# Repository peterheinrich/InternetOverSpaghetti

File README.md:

# IP_Over_Spaghetti
Transmitting IP packages using two spaghetti as transport medium

Actually this is rather RS232 over spaghetti. But using the SLIP protocol, some USB-to-RS232 adapters and two Linux machines, one can easily tunnel IP over RS232, thus effectively tunneling IP over the spaghetti.

The whole chain looks like this:
SLIP(Linux) -> FTDI (USB<->RS232) -> ATMega328P -> Relais -> Spaghetti -> Optical Sensor -> ATMega328P -> FTDI (USB<->RS232) -> SLIP(Linux)

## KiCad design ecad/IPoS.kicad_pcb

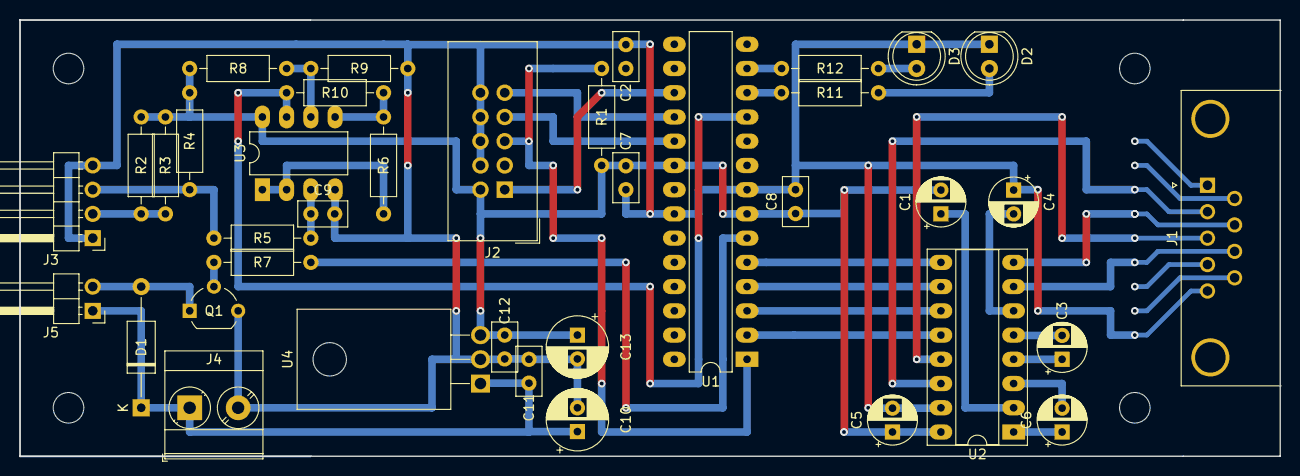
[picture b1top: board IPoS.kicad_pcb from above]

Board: 2 copper layers, 132.1 x 45.7 mm, 42 parts (0 on the bottom side), 35 nets.

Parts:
C1, C3, C4, C5, C6: 1u; CP_Radial_D5.0mm_P2.50mm
C2, C7, C8, C9, C11, C12: 100n; C_Disc_D5.0mm_W2.5mm_P2.50mm
C10, C13: 100u; CP_Radial_D6.3mm_P2.50mm
D1: D; D_A-405_P12.70mm_Horizontal
D2: LED RD; LED_D5.0mm
D3: LED GN; LED_D5.0mm
J1: RS232; DSUB-9_Female_Horizontal_P2.77x2.84mm_EdgePinOffset4.94mm_H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
J2: AVR-ISP-10; IDC-Header_2x05_P2.54mm_Vertical
J3: Optical Sensor; PinHeader_1x04_P2.54mm_Horizontal
J4: Power In; TerminalBlock_Phoenix_MKDS-3-2-5.08_1x02_P5.08mm_Horizontal
J5: Relais; PinHeader_1x02_P2.54mm_Horizontal
MH1, MH2, MH3, MH4: MountingHole; MountingHole_3.2mm_M3
Q1: BC547; TO-92_Wide
R1, R5, R10: 10K; R_Axial_DIN0207_L6.3mm_D2.5mm_P10.16mm_Horizontal
R2, R3: 150; R_Axial_DIN0207_L6.3mm_D2.5mm_P10.16mm_Horizontal
R4, R7, R8, R9: 3K3; R_Axial_DIN0207_L6.3mm_D2.5mm_P10.16mm_Horizontal
R6, R11, R12: 1K; R_Axial_DIN0207_L6.3mm_D2.5mm_P10.16mm_Horizontal
U1: ATMega328; DIP-28_W7.62mm_LongPads
U2: MAX232; DIP-16_W7.62mm_Socket_LongPads
U3: LM358; DIP-8_W7.62mm_LongPads
U4: L7805; TO-220F-3_Horizontal_TabDown

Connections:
+5V: C1.2, C5.1, C7.1, C8.1, C12.1, C13.1, J2.2, R1.1, R2.1, R3.1, R4.1, R8.1, U1.7, U1.20, U2.16, U3.8, U4.3
+12V: C10.1, C11.1, D1.1, J4.1, J5.1, U4.1
/CTS: U1.5, U2.9
/MISO: J2.9, U1.18
/MOSI: J2.1, U1.17
/RS232_CTS: J1.8, U2.7
/RS232_RTS: J1.7, U2.8
/RS232_RXD: J1.2, U2.14
/RS232_TXD: J1.3, U2.13
/RTS: U1.4, U2.10
/RXD: U1.2, U2.12
/Spaghetti_RX: R10.1, U1.11, U3.7
/Spaghetti_TX: R7.2, U1.6
/TXD: U1.3, U2.11
GND: C2.2, C4.1, C5.2, C7.2, C8.2, C9.2, C10.2, C11.2, C12.2, C13.2, D2.1, D3.1, J1.5, J2.4, J2.6, J2.8, J2.10, J3.1, J3.4, J4.2, Q1.3, R9.2, U1.8, U1.22, U2.15, U3.4, U4.2
unnamed: C1.1, U2.2
unnamed: C2.1, J2.5, R1.2, U1.1
unnamed: C3.1, U2.4
unnamed: C3.2, U2.5
unnamed: C4.2, U2.6
unnamed: C6.1, U2.1
unnamed: C6.2, U2.3
unnamed: C9.1, R5.1, U3.3
unnamed: D1.2, J5.2, Q1.1
unnamed: D2.2, R11.1
unnamed: D3.2, R12.1
unnamed: J2.7, U1.19
unnamed: J3.2, R2.2, R3.2
unnamed: J3.3, R4.2, R5.2
unnamed: Q1.2, R7.1
unnamed: R6.2, U3.1, U3.2
unnamed: R8.2, R9.1, U3.6
unnamed: R6.1, R10.2, U3.5
unnamed: R11.2, U1.12
unnamed: R12.2, U1.13

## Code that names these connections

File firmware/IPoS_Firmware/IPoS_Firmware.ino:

#include "TimerOne.h"  

#define SPAGHETTI_RX  5
#define SPAGHETTI_TX  4
#define LED_RED       6
#define LED_GREEN     7
#define CTS           3
#define RTS           2

#define BUFFSIZE      32
#define __DEBUG__

// Global variables need 'volatile' so that they can be altered within the ISR routine
volatile int tick = 0;

volatile char tx_buff[BUFFSIZE];
volatile char tx_buff_last = 0;
volatile char tx_byte = 0;
volatile char tx_state = 0;
volatile char tx_bit = 0;
volatile char tx_blank = 0;

volatile char rx_byte = 0;
volatile char rx_state = 0;
volatile char rx_bit = 0;
volatile char rx_tick_offset = 0;

/* ********************************************************************** */
/* *** BOARD SETUP                                                    *** */
/* ********************************************************************** */
void setup() {

  // Setup board specific pins
  pinMode(SPAGHETTI_TX, OUTPUT);
  pinMode(SPAGHETTI_RX, INPUT);
  pinMode(LED_RED, OUTPUT);
  pinMode(LED_GREEN, OUTPUT);
  pinMode(CTS, INPUT);
  pinMode(RTS, OUTPUT);

  // Simple 9600 8N1
  Serial.begin(9600); 

  // Assert RTS to accept incomming bytes
  digitalWrite(RTS,LOW);
  
  // Initialize 2.5ms timer interupt and register isr
  Timer1.initialize(2500);
  Timer1.attachInterrupt(isr_timer);

}


/* ********************************************************************** */
/* *** MAIN 400Hz INTERRUPT ROUTINE                                    *** */
/* ********************************************************************** */
void isr_timer() {
  int i;

  /* ********************************************************************** */
  /* *** TRANSMIT                                                       *** */
  /* ********************************************************************** */

  // Check if buffer is full. If buffer is full it is better to lose bytes than to crash ...
  if (Serial.available() > 0 && tx_buff_last < BUFFSIZE - 1) {
    tx_buff[tx_buff_last] = Serial.read() & 0xFF;
    tx_buff_last++;
  } 

  // Some implementation take several bytes until they react on RTS deassertion. Thus, we accept only 4 bytes before deasserting RTS.
  if(tx_buff_last > 3) {
      digitalWrite(RTS,HIGH);
  }
  else {
      digitalWrite(RTS,LOW);
  }

  // A single bit is exactly 25ms long. Thus, we switch states every 10 timer ticks.
  if(tick % 10 == 0) {
    switch(tx_state) {
      case 0:
       // If buffer is nonempty, remove and transmit first byte from buffer
        if(tx_buff_last > 0) {
          tx_byte = tx_buff[0];
          // move all items to the front - yes, dumb but simple! No need for a ringbuffer whatsoever!
          for(i = 1; i < tx_buff_last; i++) {
            tx_buff[i-1] = tx_buff[i];
          }
          tx_buff_last --;
          tx_state = 1;
          tx_bit = 0;
        }
        break;
      case 1:
        // Write the start bit
        digitalWrite(SPAGHETTI_TX,HIGH);
        tx_state = 2;
        break;
      case 2:
        // Write individual bits
        digitalWrite(SPAGHETTI_TX,(tx_byte >> tx_bit) & 0x01);
        tx_bit++;
        if(tx_bit > 7) {
          tx_blank = 0;
          tx_state = 3;
          tx_bit = 0;
        }
        break;
      case 3:
        // Insert a two cycle blank
        digitalWrite(SPAGHETTI_TX,LOW);
        if(tx_blank > 1) {
          tx_state = 0;
        }
        tx_blank ++;
        break;
    }   
  }

  /* ********************************************************************** */
  /* *** RECEIVE                                                        *** */
  /* ********************************************************************** */
  
  // We scan for the start bit on any tick (400Hz)
  if(rx_state == 0) {
    if(digitalRead(SPAGHETTI_RX)) {

#ifdef __DEBUG__
      digitalWrite(LED_RED,HIGH);
      delay(1);
      digitalWrite(LED_RED,LOW);
#endif

      rx_state = 1;
      rx_byte = 0x0;
      rx_bit = 0;
      // We store the offset to the 25ms bit cycle and add some margin to scan for the next bits roughly in the middle of their heigh period.
      rx_tick_offset = ((tick + 6) % 10);  
    }
  }
  
  if(rx_state != 0 && tick % 10 == rx_tick_offset) {
    switch(rx_state) {
      case 1:
        // Waiting for the start bit to clear (dummy state)
        rx_state = 2;
        break;
      case 2:
      
#ifdef __DEBUG__  
        digitalWrite(LED_GREEN,HIGH);
        delay(1);
        digitalWrite(LED_GREEN,LOW);
#endif
        // Reading all the bits
        rx_byte = rx_byte | (digitalRead(SPAGHETTI_RX) << rx_bit);       
        rx_bit ++;
        
        if(rx_bit > 7) {
          Serial.write(rx_byte);
          rx_state = 3;
        }
        break;
      case 3:
        // Waiting for last transferred bit to clear (dummy state)
        rx_state = 0;
        rx_bit = 0;
        break;
    }   
  }

  /* ********************************************************************** */
  /* *** HOUSE KEEPING                                                  *** */
  /* ********************************************************************** */

  // Increment tick counter and roll over
  tick ++;
  if(tick >= 1000) tick = 0;
}

// Nothing left to be done. Just an empty loop ...
void loop() {
    
}

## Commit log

2019-08-05 Correcting some comments.
2019-08-05 Correcting comment.
2019-08-05 Adding gitignore
2020-12-30 Rotated Image
2024-02-06 Update README.md
    Corrected typo ...
